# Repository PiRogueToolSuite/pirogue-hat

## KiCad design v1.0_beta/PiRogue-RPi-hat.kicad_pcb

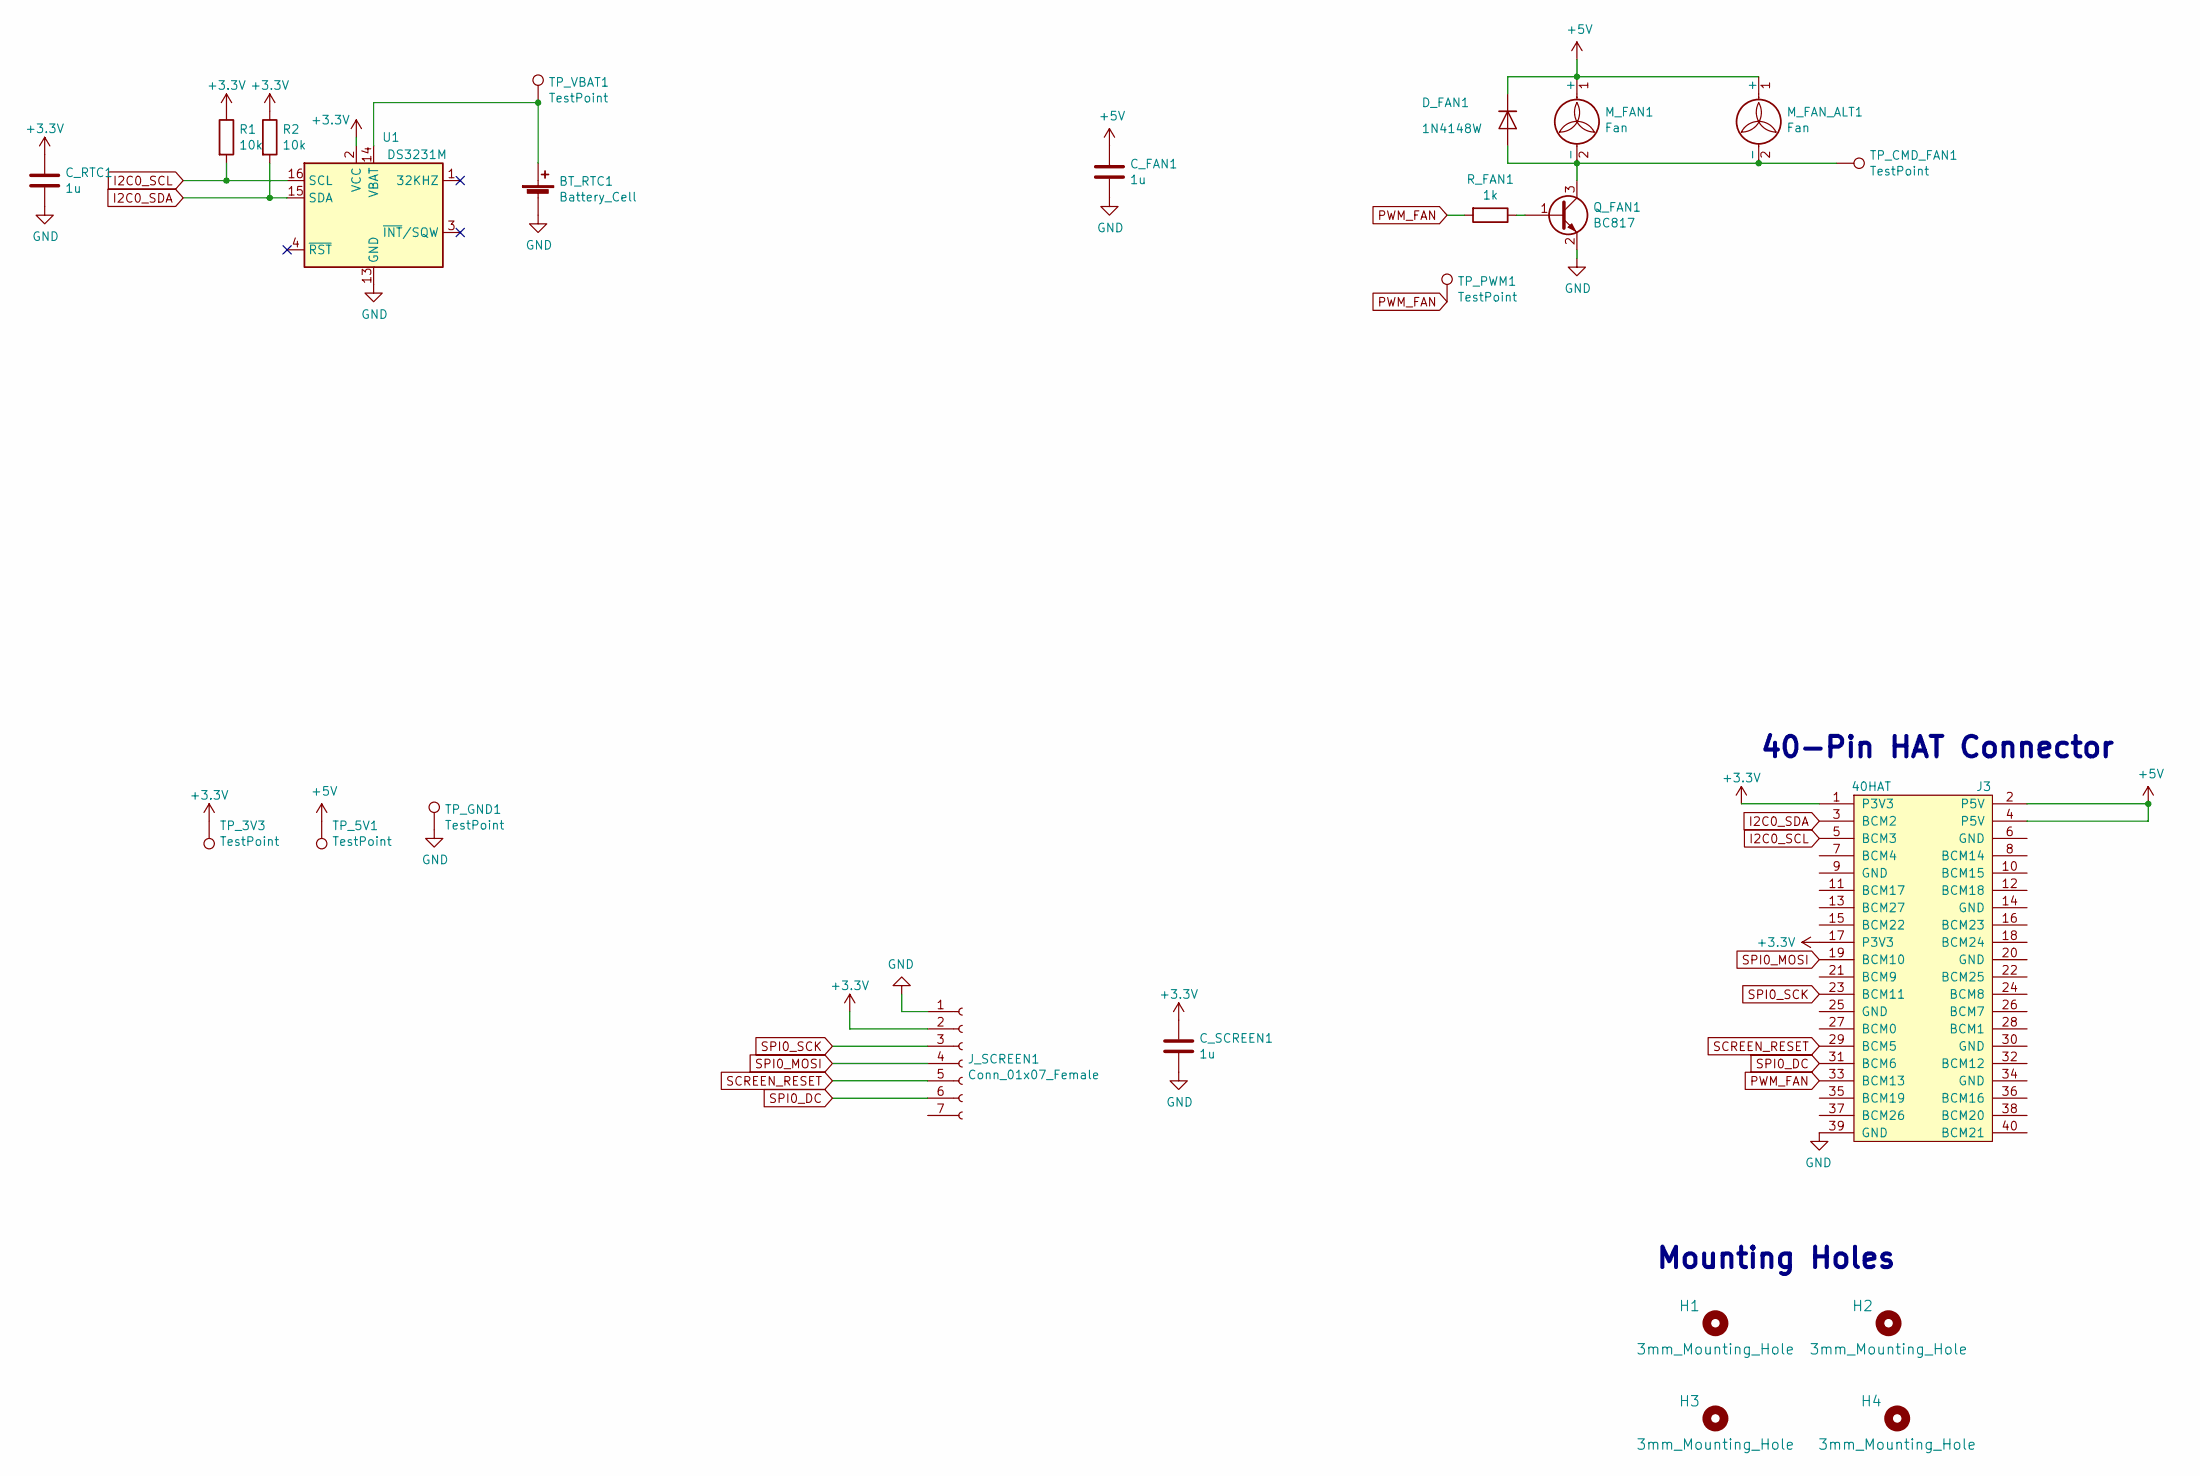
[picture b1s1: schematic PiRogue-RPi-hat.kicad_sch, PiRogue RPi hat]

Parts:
BT_RTC1: Battery_Cell; Mikroteck-CR1220
C_FAN1: 1u; C_0805_2012Metric_Pad1.15x1.40mm_HandSolder
C_RTC1: 1u; C_0805_2012Metric_Pad1.15x1.40mm_HandSolder
C_SCREEN1: 1u; C_0805_2012Metric_Pad1.15x1.40mm_HandSolder
D_FAN1: 1N4148W; D_SOD-123
H1, H2, H3, H4: 3mm_Mounting_Hole; MountingHole_3.2mm_M3_Pad
J3: 40HAT; PinSocket_2x20_P2.54mm_Vertical
J_SCREEN1: Conn_01x07_Female; PinHeader_1x07_P2.54mm_Vertical
M_FAN1: Fan; PinHeader_1x02_P2.54mm_Vertical
M_FAN_ALT1: Fan; PinHeader_1x02_P2.54mm_Vertical
Q_FAN1: BC817; SOT-23
R1, R2: 10k; R_0805_2012Metric_Pad1.15x1.40mm_HandSolder
R_FAN1: 1k; R_0805_2012Metric_Pad1.15x1.40mm_HandSolder
TP_3V3, TP_5V1: TestPoint; TestPoint_Pad_D2.0mm
TP_CMD_FAN1: TestPoint; TestPoint_Pad_D2.0mm
TP_GND1: TestPoint; TestPoint_Pad_D2.0mm
TP_PWM1: TestPoint; TestPoint_Pad_D2.0mm
TP_VBAT1: TestPoint; TestPoint_Pad_D2.0mm
U1: DS3231M; SOIC-16W_7.5x10.3mm_P1.27mm

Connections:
+3V3: C_RTC1.1, C_SCREEN1.1, J3.1 (P3V3), J3.17 (P3V3), J_SCREEN1.2, R1.1, R2.1, TP_3V3.1, U1.2 (VCC)
+5V: C_FAN1.1, D_FAN1.1 (K), J3.2 (P5V), J3.4 (P5V), M_FAN1.1 (+), M_FAN_ALT1.1 (+), TP_5V1.1
GND: BT_RTC1.2 (-), C_FAN1.2, C_RTC1.2, C_SCREEN1.2, J3.39 (GND), J_SCREEN1.1, Q_FAN1.2 (E), TP_GND1.1, U1.5 (GND), U1.6 (GND), U1.7 (GND), U1.8 (GND), U1.9 (GND), U1.10 (GND), U1.11 (GND), U1.12 (GND), U1.13 (GND)
I2C0_SCL: J3.5 (BCM3), R1.2, U1.16 (SCL)
I2C0_SDA: J3.3 (BCM2), R2.2, U1.15 (SDA)
unnamed: BT_RTC1.1 (+), TP_VBAT1.1, U1.14 (VBAT)
unnamed: D_FAN1.2 (A), M_FAN1.2 (-), M_FAN_ALT1.2 (-), Q_FAN1.3 (C), TP_CMD_FAN1.1
unnamed: Q_FAN1.1 (B), R_FAN1.1
PWM_FAN: J3.33 (BCM13), R_FAN1.2, TP_PWM1.1
SCREEN_RESET: J3.29 (BCM5), J_SCREEN1.5
SPI0_DC: J3.31 (BCM6), J_SCREEN1.6
SPI0_MOSI: J3.19 (BCM10), J_SCREEN1.4
SPI0_SCK: J3.23 (BCM11), J_SCREEN1.3

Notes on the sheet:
40-Pin HAT Connector
Mounting Holes

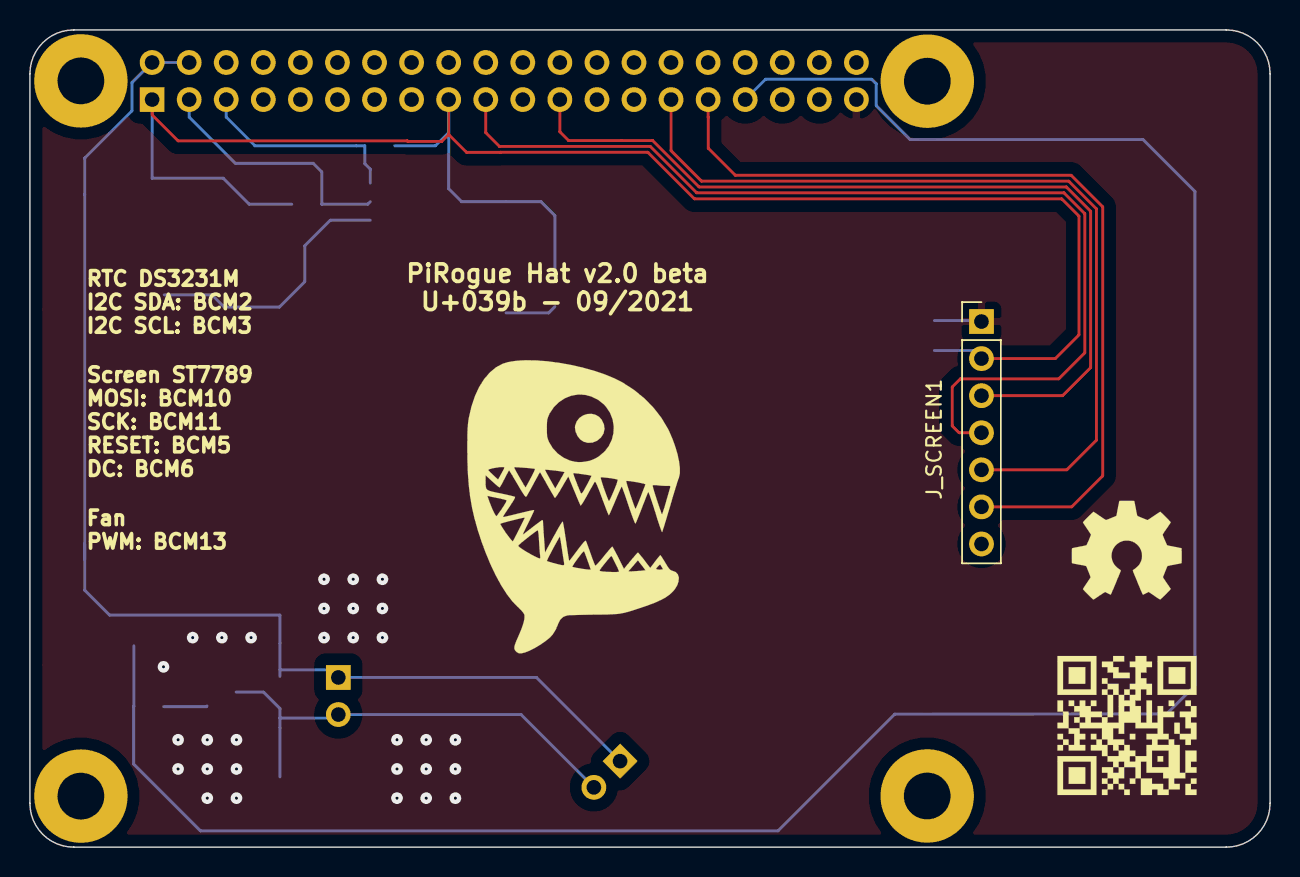
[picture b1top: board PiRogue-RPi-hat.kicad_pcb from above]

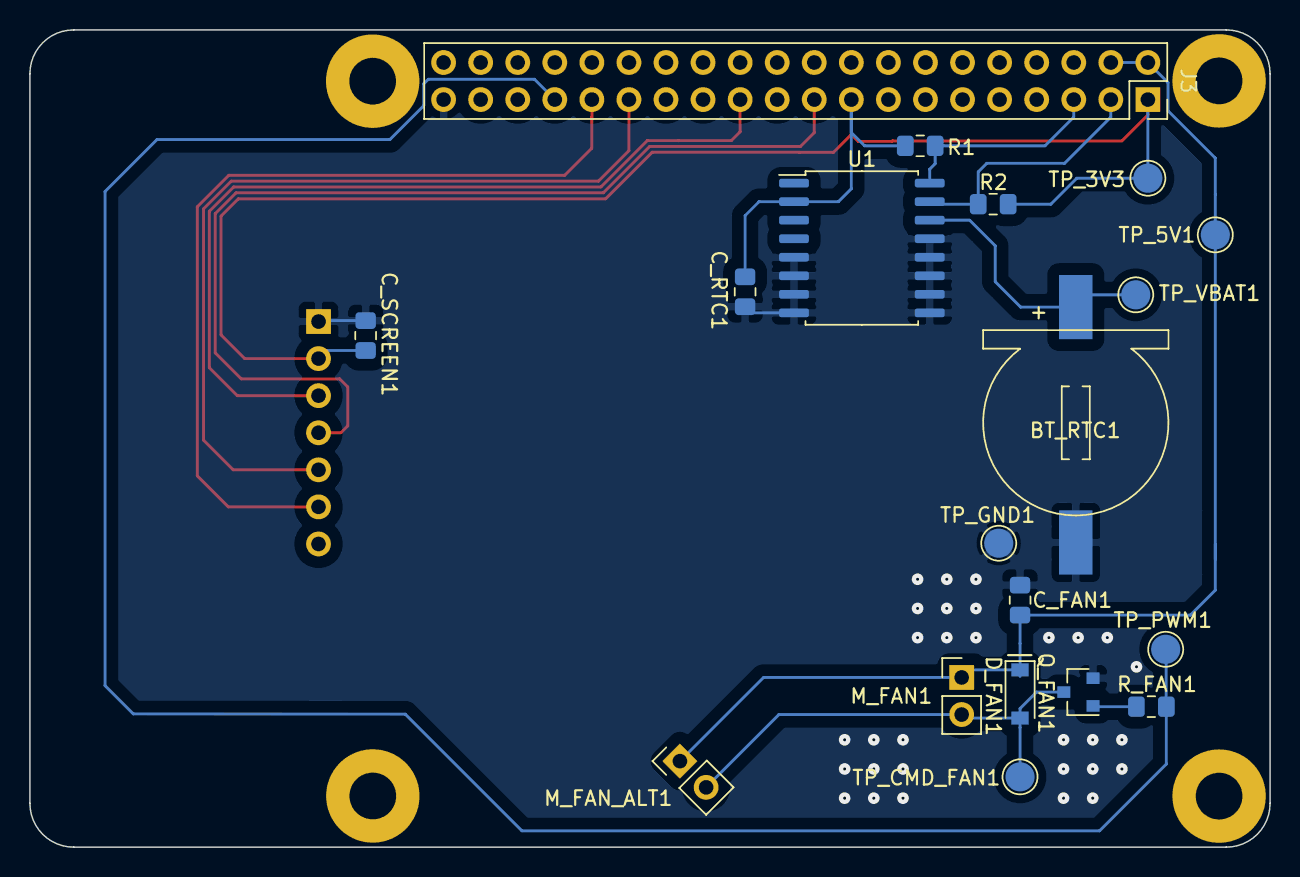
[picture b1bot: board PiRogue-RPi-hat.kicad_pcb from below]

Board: 4 copper layers, 85.0 x 56.0 mm, 24 parts (19 on the bottom side), 13 nets.

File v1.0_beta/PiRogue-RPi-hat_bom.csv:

Id;Reference;Footprint;Qty;Value
6;J3;PinSocket_2x20_P2.54mm_Vertical;1;40HAT
7;BT_RTC1;Mikroteck-CR1220;1;Battery_Cell
8;C_RTC1,C_SCREEN1,C_FAN1;C_0805_2012Metric_Pad1.15x1.40mm_HandSolder;3;1u
9;D_FAN1;D_SOD-123;1;1N4148W
10;M_FAN1,M_FAN_ALT1;PinHeader_1x02_P2.54mm_Vertical;2;Fan
11;Q_FAN1;SOT-23;1;BC817
12;R1,R2;R_0805_2012Metric_Pad1.15x1.40mm_HandSolder;2;10k
13;R_FAN1;R_0805_2012Metric_Pad1.15x1.40mm_HandSolder;1;1k
14;U1;SOIC-16W_7.5x10.3mm_P1.27mm;1;DS3231M

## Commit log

2022-03-07 Add manufacturing files
2022-03-07 Change license
2022-03-20 Add bill of material
